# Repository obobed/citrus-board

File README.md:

# Citrus Board
A RP2350 based devboard with LiPO and HSTX support!

## Why I made this + features
I made this since I wanted an alternative to the mainstream RP2350/2040 boards (like the xiaos), but with support for the more niche features of the chip that aren't exposed on almost all of them, like HSTX ([page 1203](https://pip-assets.raspberrypi.com/categories/1214-rp2350/documents/RP-008373-DS-2-rp2350-datasheet.pdf#page=1203)), which allows you to easily add an external display (or even camera) without sacrificing a lot the small computing power of the small chip, or even LiPo support (although most boards have it (except for the Raspberry Pi Pico), many don't have a dedicated charging IC to both support the chip's usage and to charge the battery at the same time). Additionally, it has 26 pins, indicator LEDs for charging and power, the HSTX 22pin ribbon cable terminal (which can be used with libraries like [this](https://github.com/adafruit/Adafruit-DVI-HSTX) from Adafruit) and a debug connector that is exactly compatible with the oficial [Raspberry Pi Debug Probe
](https://www.raspberrypi.com/documentation/microcontrollers/debug-probe.html).

## Repo Structure
* [/pcb](/pcb) - My KiCad design files
* [/production](/production) - Everything you need to manufacture your own! Includes gerbers, a bom and positioning files
* [/images](/images) - Images of my PCB and 3D view! (Zine is in [/zine](/zine))
* [/plots](/plots) - Schematic plot (SVG and PNG) and separate layer outlines in DXF format
* [/cad](/cad) - A step file of my PCB for reference when building projects around it
* [/bom](/bom) - My BOMs (like the below tables) stored in a CSV format

## Schematic

## PCB

## 3D View

## Assembly
Welll this is a devboard, so there isn't much to assemble, but if you want to hand solder (definitely do not reccomend) instead of doing PCBA, follow these steps (my bom at the bottom accounts for using PCBA and not hand soldering)
Prerequisite:
* Purchase a stencil from JLCPCB alongside your order, and use the [LCSC BOM](/bom/component_bom.csv) to buy the separate parts from LCSC

1. Apply the paste
2. Place components
3. Use your preferred equipment (oven, hot-air gun or hotplate) to solder the board
4. Done!

(this section is here because the submission precheck kept giving me warning about this)

## BOM
### Component BOM
| Designator                                           | Footprint                                            | Quantity | Value                                | LCSC Part # | Total Cost (USD) |
|------------------------------------------------------|------------------------------------------------------|----------|--------------------------------------|-------------|------------------|
| C1, C2                                               | 0402                                                 | 2        | 15p                                  | C1548       | 0.0088           |
| C10, C12, C14, C5, C6, C9                            | 0402                                                 | 6        | 4.7u                                 | C23733      | 0.2328           |
| C11, C13, C17, C18, C19, C20, C21, C22, C23, C27, C8 | 0402                                                 | 11       | 100n                                 | C307331     | 0.0682           |
| C15, C16, C4, C7                                     | 0805                                                 | 4        | 10u                                  | C1713       | 1.6848           |
| C3                                                   | 603                                                  | 1        | 1u                                   | C1592       | 0.0312           |
| D1                                                   | 0805                                                 | 1        | ORANGE                               | C2296       | 0.0304           |
| D2                                                   | 0603                                                 | 1        | RED                                  | C2286       | 0.0144           |
| J1                                                   | USB-C-SMD_TYPE-C-6PIN-2MD-073                        | 1        | SHOU_HAN_USB_C_Receptacle_USB2.0_16P |             | 0.2205           |
| J2                                                   | JST_PH_B2B-PH-K_1x02_P2.00mm_Vertical                | 1        | Conn_01x02                           | C131337     | 0.1041           |
| J3                                                   | JST_SH_SM03B-SRSS-TB_1x03-1MP_P1.00mm_Horizontal     | 1        | Conn_01x03_MountingPin               | C160389     | 1.3305           |
| J4                                                   | CONN-SMD_AFC01-S22FCA-HF                             | 1        | 0.5mm FPC                            | C49260526   | 0.2614           |
| L1                                                   | IND-SMD_L3.9-W3.9                                    | 1        | 2.2uH                                | C20416998   | 2.2494           |
| L2                                                   | IND-SMD_L2.0-W1.6_AOTA-B201610S3R3-101-T             | 1        | 3.3uH                                | C42411119   | 1.4085           |
| R1                                                   | 0402                                                 | 1        | 1.18k                                | C270651     | 0.01             |
| R10                                                  | 0402                                                 | 1        | 1k                                   | C270651     | 0.0022           |
| R11                                                  | 0402                                                 | 1        | 33R                                  | C25105      | 0.002            |
| R12, R15, R17, R6                                    | 0402                                                 | 4        | 10k                                  | C25744      | 0.0232           |
| R13, R14                                             | 0402                                                 | 2        | 27R                                  | C25100      | 0.02             |
| R16                                                  | 0805                                                 | 1        | 0                                    | C17477      | 0.006            |
| R2                                                   | 0402                                                 | 1        | 1.13k                                | C67014      | 0.018            |
| R3                                                   | 0402                                                 | 1        | 50                                   | C227387     | 0.016            |
| R4, R5                                               | 0402                                                 | 2        | 5k1                                  | C25905      | 0.0036           |
| R7                                                   | 0402                                                 | 1        | 1.5k                                 | C25867      | 0.0022           |
| R8                                                   | 0402                                                 | 1        | 100                                  | C25076      | 0.0024           |
| R9                                                   | 0402                                                 | 1        | 100k                                 | C25741      | 0.0078           |
| SW1, SW2                                             | SW-SMD_L3.9-W3.0-P4.45                               | 2        | SW_Push                              | C720477     | 0.2208           |
| U1                                                   | VQFN-16-1EP_3x3mm_P0.5mm_EP1.6x1.6mm                 | 1        | BQ24074RGT                           | C54313      | 4.7728           |
| U2                                                   | Texas_DRC0010J_ThermalVias                           | 1        | TPS63000-Q1                          | C28060      | 3.5514           |
| U3                                                   | RP2350-QFN-60-1EP_7x7_P0.4mm_EP3.4x3.4mm_ThermalVias | 1        | RP2354A                              | C41378174   | 2.678            |
| U4                                                   | SOIC-8_5.3x5.3mm_P1.27mm                             | 1        | W25Q128JVS                           | C97521      | 4.8534           |
| Y1                                                   | Crystal_SMD_3225-4Pin_3.2x2.5mm                      | 1        | Crystal_GND24                        | C20625731   | 1.4655           |
|||||||
| Total                                                |                                                      |          |                                      |             | 25.3003          |

### Overall BOM
| Item              | Cost (USD) | Notes |
|-------------------|------------|-------|
| PCB               | $7         |       |
| Castellated Edges | $37.70     | Not strictly required, see note 2 [here](https://jlcpcb.com/help/article/what-is-castellated-holes). If you want to save on costs, it is not necessary, but will result in a slightly lower quality finish. |
| PCB Shipping      | $1.50      |       |
| PCBA              | $80.72     |       |
||||
| Total | $89.22 ||

## Zine!!

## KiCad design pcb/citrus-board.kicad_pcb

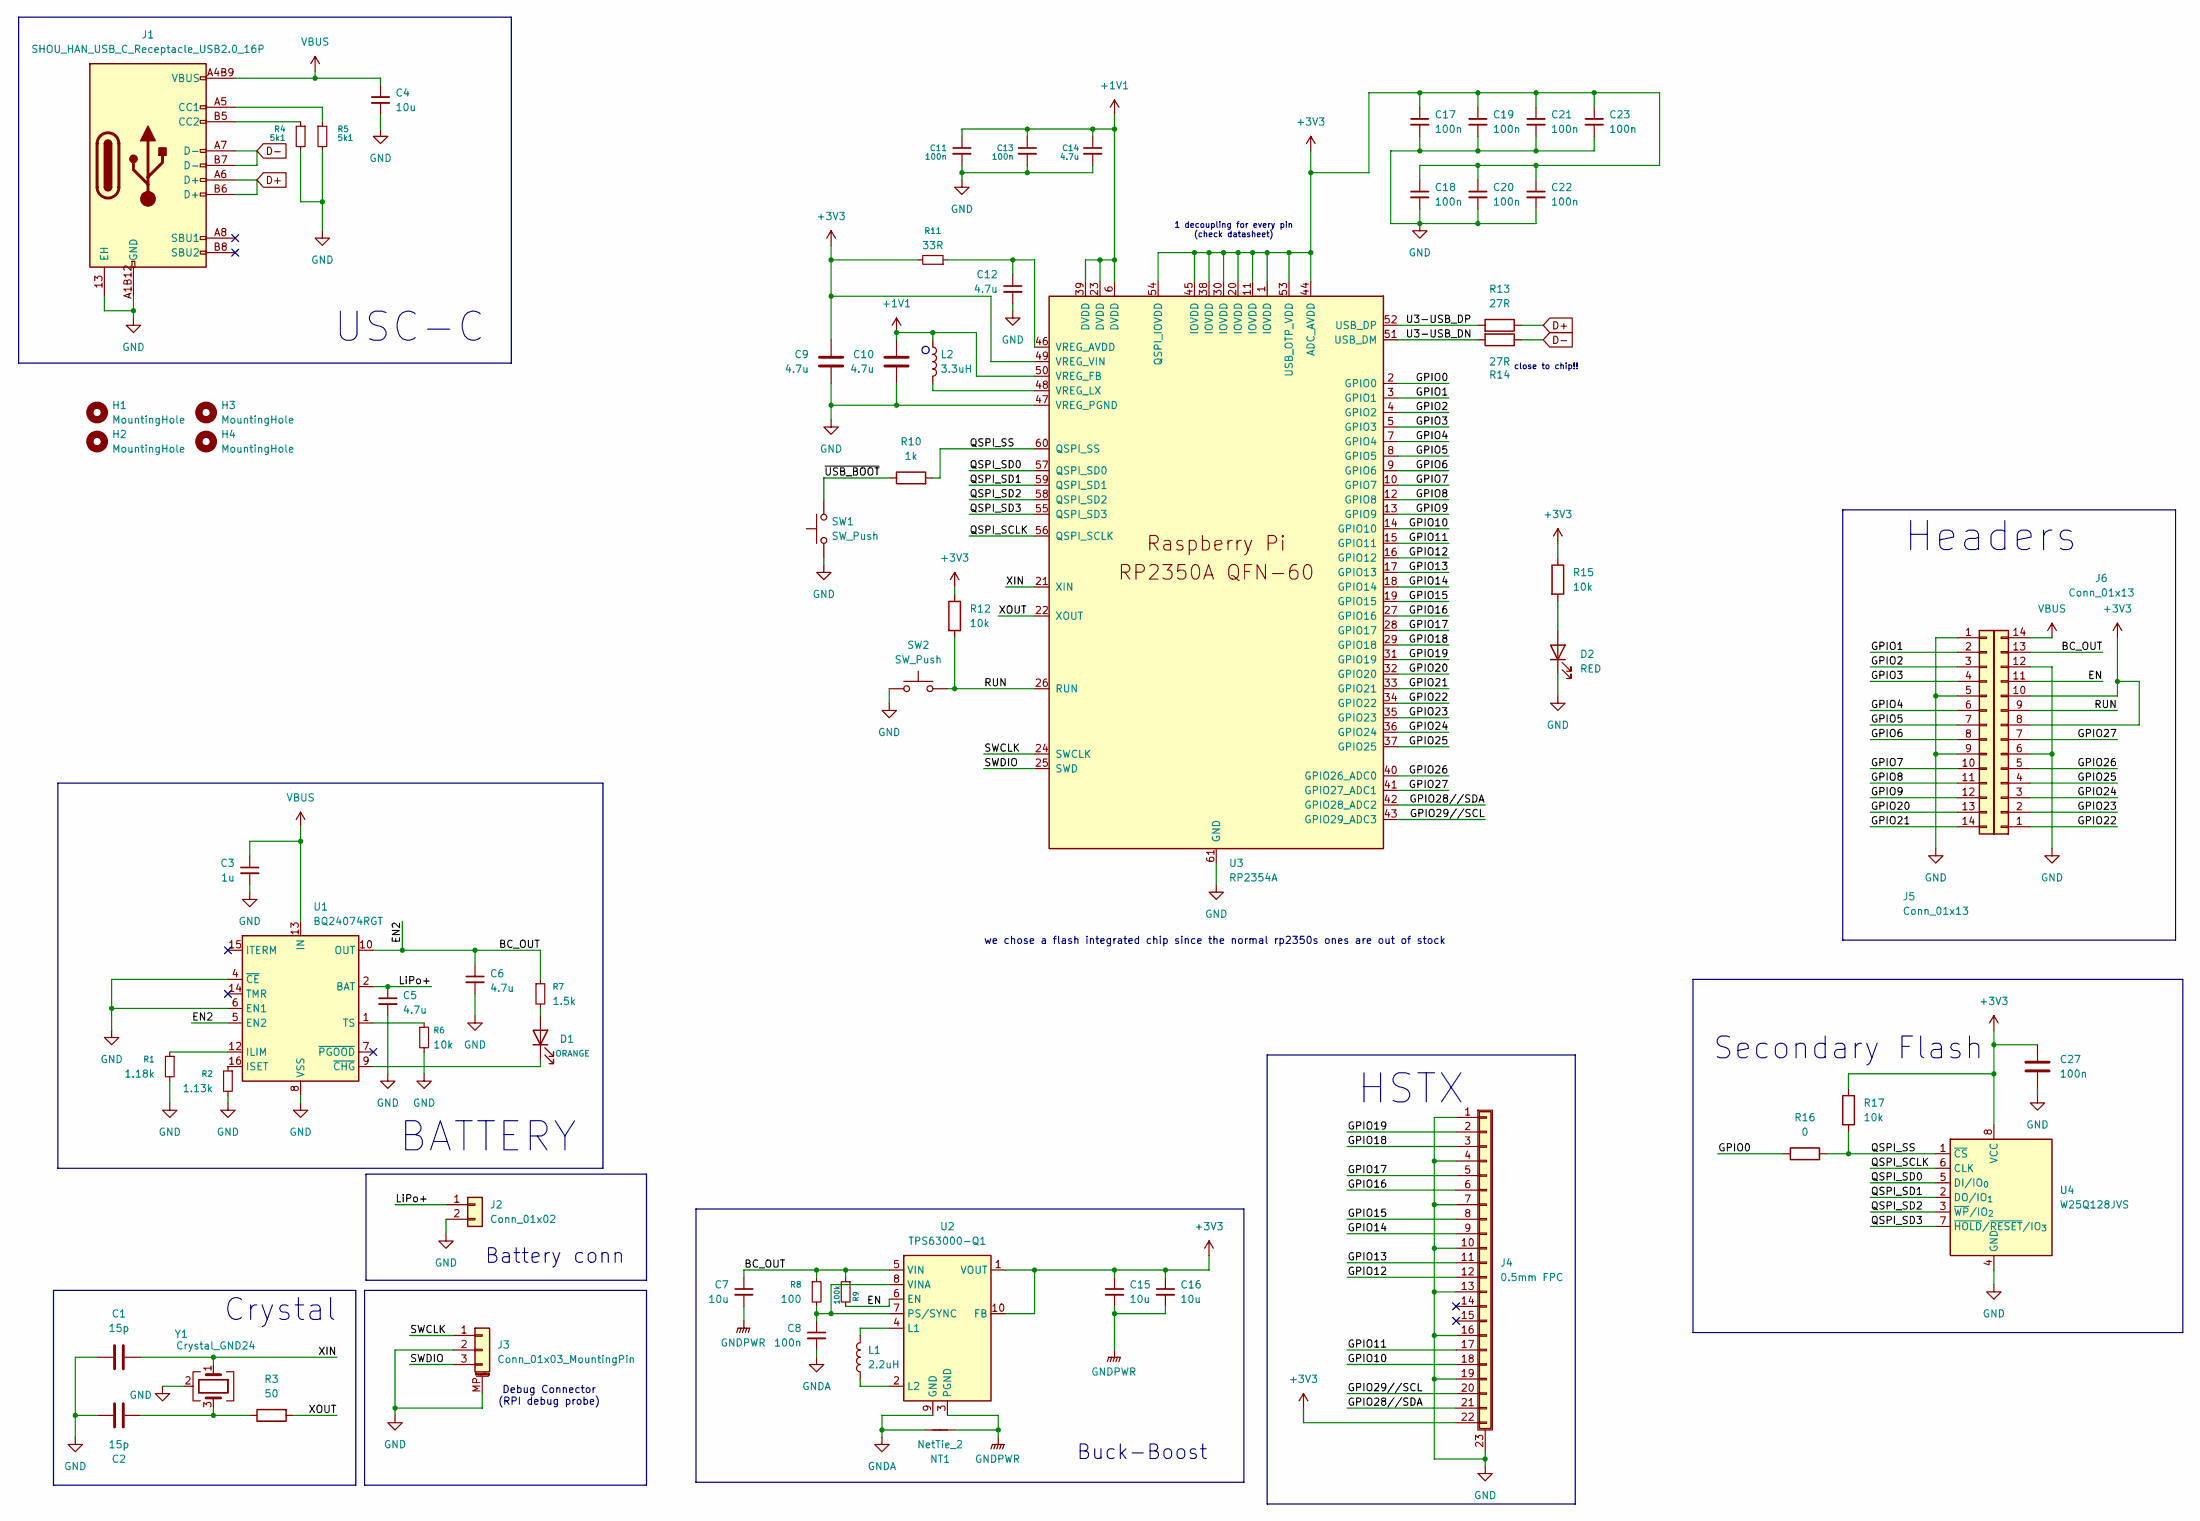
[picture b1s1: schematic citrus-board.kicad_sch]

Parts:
C1, C2: 15p; C_0402_1005Metric; LCSC Part # C1548
C3: 1u; C_0603_1608Metric; LCSC Part # C1592
C4, C7, C15, C16: 10u; C_0805_2012Metric; LCSC Part # C1713
C5, C6, C9, C10, C12, C14: 4.7u; C_0402_1005Metric; LCSC Part # C23733
C8, C11, C13, C17, C18, C19, C20, C21, C22, C23, C27: 100n; C_0402_1005Metric; LCSC Part # C307331
D1: ORANGE; LED_0805_2012Metric; LCSC Part # C2296
D2: RED; LED_0603_1608Metric; LCSC Part # C2286
H1, H2, H3, H4: MountingHole; MountingHole_2.1mm
J1: SHOU_HAN_USB_C_Receptacle_USB2.0_16P; USB-C-SMD_TYPE-C-6PIN-2MD-073; LCSC Part # C2765186
J2: Conn_01x02; JST_PH_B2B-PH-K_1x02_P2.00mm_Vertical; LCSC Part # C131337
J3: Conn_01x03_MountingPin; JST_SH_SM03B-SRSS-TB_1x03-1MP_P1.00mm_Horizontal; LCSC Part # C160389
J4: 0.5mm FPC; CONN-SMD_AFC01-S22FCA-HF; LCSC Part # C49260526
J5, J6: Conn_01x13; Conn_01x14_Castellated
L1: 2.2uH; IND-SMD_L3.9-W3.9; LCSC Part # C20416998
L2: 3.3uH; IND-SMD_L2.0-W1.6_AOTA-B201610S3R3-101-T; LCSC Part # C42411119
NT1: NetTie_2; NetTie-2_SMD_Pad0.5mm
R1: 1.18k; R_0402_1005Metric; LCSC Part # C270651
R2: 1.13k; R_0402_1005Metric; LCSC Part # C67014
R3: 50; R_0402_1005Metric; LCSC Part # C227387
R4, R5: 5k1; R_0402_1005Metric; LCSC Part # C25905
R6, R12, R15, R17: 10k; R_0402_1005Metric; LCSC Part # C25744
R7: 1.5k; R_0402_1005Metric; LCSC Part # C25867
R8: 100; R_0402_1005Metric; LCSC Part # C25076
R9: 100k; R_0402_1005Metric; LCSC Part # C25741
R10: 1k; R_0402_1005Metric; LCSC Part # C270651
R11: 33R; R_0402_1005Metric; LCSC Part # C25105
R13, R14: 27R; R_0402_1005Metric; LCSC Part # C25100
R16: 0; R_0805_2012Metric; LCSC Part # C17477
SW1, SW2: SW_Push; SW-SMD_L3.9-W3.0-P4.45; LCSC Part # C720477
U1: BQ24074RGT; VQFN-16-1EP_3x3mm_P0.5mm_EP1.6x1.6mm; LCSC Part # C54313
U2: TPS63000-Q1; Texas_DRC0010J_ThermalVias; LCSC Part # C28060
U3: RP2354A; RP2350-QFN-60-1EP_7x7_P0.4mm_EP3.4x3.4mm_ThermalVias; LCSC Part # C41378174
U4: W25Q128JVS; SOIC-8_5.3x5.3mm_P1.27mm; LCSC Part # C97521
Y1: Crystal_GND24; Crystal_SMD_3225-4Pin_3.2x2.5mm; LCSC Part # C20625731

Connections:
+1V1: C10.1, C11.1, C13.1, C14.1, L2.1, U3.6 (DVDD), U3.23 (DVDD), U3.39 (DVDD), U3.50 (VREG_FB)
+3V3: C9.1, C15.1, C16.1, C17.1, C18.1, C19.1, C20.1, C21.1, C22.1, C23.1, C27.1, J4.22, J6.8, J6.10, R11.2, R12.1, R15.1, R17.2, U2.1 (VOUT), U2.10 (FB), U3.1 (IOVDD), U3.11 (IOVDD), U3.20 (IOVDD), U3.30 (IOVDD), U3.38 (IOVDD), U3.44 (ADC_AVDD), U3.45 (IOVDD), U3.49 (VREG_VIN), U3.53 (USB_OTP_VDD), U3.54 (QSPI_IOVDD), U4.8 (VCC)
/BC_OUT: C6.1, C7.1, J6.13, R7.1, R8.1, R9.1, U1.5 (EN2), U1.10 (OUT), U1.11 (OUT), U2.5 (VIN)
/EN: J6.11, R9.2, U2.6 (EN)
/GPIO0: R16.1, U3.2 (GPIO0)
/GPIO1: J5.2, U3.3 (GPIO1)
/GPIO2: J5.3, U3.4 (GPIO2)
/GPIO3: J5.4, U3.5 (GPIO3)
/GPIO4: J5.6, U3.7 (GPIO4)
/GPIO5: J5.7, U3.8 (GPIO5)
/GPIO6: J5.8, U3.9 (GPIO6)
/GPIO7: J5.10, U3.10 (GPIO7)
/GPIO8: J5.11, U3.12 (GPIO8)
/GPIO9: J5.12, U3.13 (GPIO9)
/GPIO10: J4.18, U3.14 (GPIO10)
/GPIO11: J4.17, U3.15 (GPIO11)
/GPIO12: J4.12, U3.16 (GPIO12)
/GPIO13: J4.11, U3.17 (GPIO13)
/GPIO14: J4.9, U3.18 (GPIO14)
/GPIO15: J4.8, U3.19 (GPIO15)
/GPIO16: J4.6, U3.27 (GPIO16)
/GPIO17: J4.5, U3.28 (GPIO17)
/GPIO18: J4.3, U3.29 (GPIO18)
/GPIO19: J4.2, U3.31 (GPIO19)
/GPIO20: J5.13, U3.32 (GPIO20)
/GPIO21: J5.14, U3.33 (GPIO21)
/GPIO22: J6.1, U3.34 (GPIO22)
/GPIO23: J6.2, U3.35 (GPIO23)
/GPIO24: J6.3, U3.36 (GPIO24)
/GPIO25: J6.4, U3.37 (GPIO25)
/GPIO26: J6.5, U3.40 (GPIO26_ADC0)
/GPIO27: J6.7, U3.41 (GPIO27_ADC1)
/GPIO28//SDA: J4.21, U3.42 (GPIO28_ADC2)
/GPIO29//SCL: J4.20, U3.43 (GPIO29_ADC3)
/LiPo+: C5.1, J2.1, U1.2 (BAT), U1.3 (BAT)
/QSPI_SCLK: U3.56 (QSPI_SCLK), U4.6 (CLK)
/QSPI_SD0: U3.57 (QSPI_SD0), U4.5 (DI/IO_{0})
/QSPI_SD1: U3.59 (QSPI_SD1), U4.2 (DO/IO_{1})
/QSPI_SD2: U3.58 (QSPI_SD2), U4.3 (~WP/IO_{2})
/QSPI_SD3: U3.55 (QSPI_SD3), U4.7 (~HOLD/~RESET/IO_{3})
/QSPI_SS: R10.2, R16.2, R17.1, U3.60 (QSPI_SS), U4.1 (~CS)
/RUN: J6.9, R12.2, SW2.2, U3.26 (RUN)
/SWCLK: J3.1, U3.24 (SWCLK)
/SWDIO: J3.3, U3.25 (SWD)
/U3-USB_DN: R14.2, U3.51 (USB_DM)
/U3-USB_DP: R13.2, U3.52 (USB_DP)
/XIN: C1.2, U3.21 (XIN), Y1.1
/XOUT: R3.2, U3.22 (XOUT)
/~USB_BOOT: R10.1, SW1.2
D+: J1.A6 (D+), J1.B6 (D+), R13.1
D-: J1.A7 (D-), J1.B7 (D-), R14.1
GND: C1.1, C2.1, C3.2, C4.2, C5.2, C6.2, C9.2, C10.2, C11.2, C12.2, C13.2, C14.2, C17.2, C18.2, C19.2, C20.2, C21.2, C22.2, C23.2, C27.2, D2.1 (K), J1.13 (EH), J1.14 (EH), J1.A1B12 (GND), J1.B1A12 (GND), J2.2, J3.2, J3.MP (MountPin), J4.1, J4.4, J4.7, J4.10, J4.13, J4.16, J4.19, J4.23 (Shield), J4.24 (Shield), J5.1, J5.5, J5.9, J6.6, J6.12, R1.2, R2.2, R4.2, R5.2, R6.2, SW1.1, SW2.1, U1.4 (~CE), U1.6 (EN1), U1.8 (VSS), U1.17 (VSS), U3.47 (VREG_PGND), U3.61 (GND), U4.4 (GND), Y1.2 (G), Y1.4 (G)
GNDA: C8.2, NT1.1, U2.9 (GND)
GNDPWR: C7.2, C15.2, C16.2, NT1.2, U2.3 (PGND), U2.11 (PGND)
unnamed: C2.2, R3.1, Y1.3
unnamed: D1.2 (A), R7.2
unnamed: D1.1 (K), U1.9 (~CHG)
unnamed: D2.2 (A), R15.2
unnamed: J1.A5 (CC1), R5.1
unnamed: J1.B5 (CC2), R4.1
unnamed: R1.1, U1.12 (ILIM)
unnamed: R2.1, U1.16 (ISET)
unnamed: R6.1, U1.1 (TS)
unnamed: L1.2, U2.4 (L1)
unnamed: L1.1, U2.2 (L2)
unnamed: C8.1, R8.2, U2.7 (PS/SYNC), U2.8 (VINA)
unnamed: C12.1, R11.1, U3.46 (VREG_AVDD)
unnamed: L2.2, U3.48 (VREG_LX)
VBUS: C3.1, C4.1, J1.A4B9 (VBUS), J1.B4A9 (VBUS), J6.14, U1.13 (IN)

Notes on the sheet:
HSTX
USC-C
Headers
Crystal
1 decoupling for every pin (check datasheet)
close to chip!!
Debug Connector (RPI debug probe)
Buck-Boost
Battery conn
we chose a flash integrated chip since the normal rp2350s ones are out of stock
Secondary Flash
BATTERY

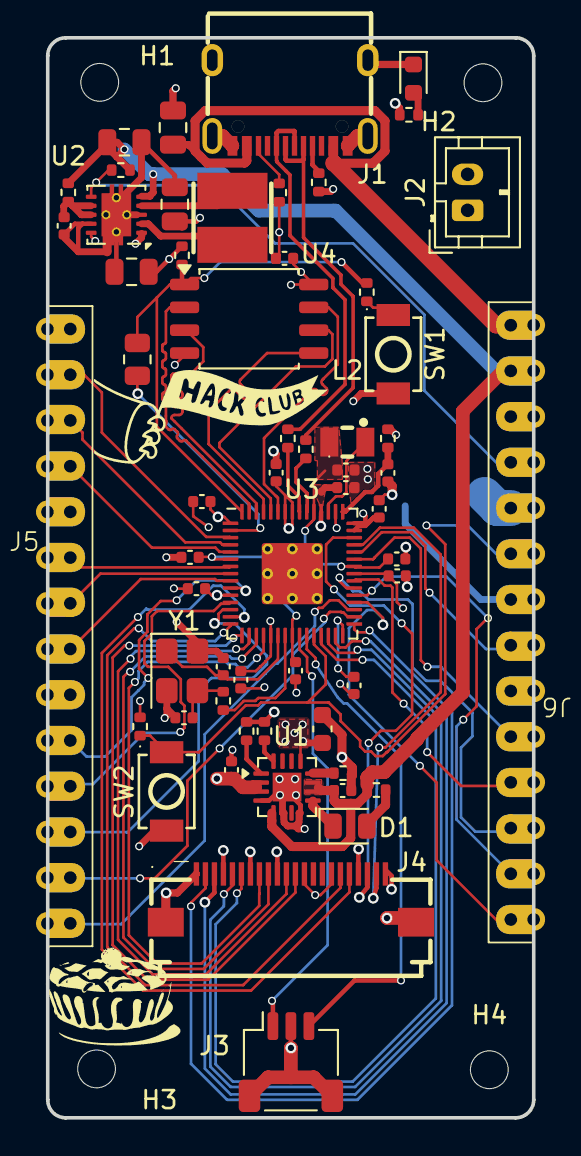
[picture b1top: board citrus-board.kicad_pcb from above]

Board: 4 copper layers, 27.0 x 60.0 mm, 63 parts (0 on the bottom side), 69 nets.

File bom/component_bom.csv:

Designator,Footprint,Quantity,Value,LCSC Part #,Total Cost (USD)
"C1, C2",0402,2,15p,C1548,0.0088
"C10, C12, C14, C5, C6, C9",0402,6,4.7u,C23733,0.2328
"C11, C13, C17, C18, C19, C20, C21, C22, C23, C27, C8",0402,11,100n,C307331,0.0682
"C15, C16, C4, C7",0805,4,10u,C1713,1.6848
C3,603,1,1u,C1592,0.0312
D1,0805,1,ORANGE,C2296,0.0304
D2,0603,1,RED,C2286,0.0144
J1,USB-C-SMD_TYPE-C-6PIN-2MD-073,1,SHOU_HAN_USB_C_Receptacle_USB2.0_16P,,0.2205
J2,JST_PH_B2B-PH-K_1x02_P2.00mm_Vertical,1,Conn_01x02,C131337,0.1041
J3,JST_SH_SM03B-SRSS-TB_1x03-1MP_P1.00mm_Horizontal,1,Conn_01x03_MountingPin,C160389,1.3305
J4,CONN-SMD_AFC01-S22FCA-HF,1,0.5mm FPC,C49260526,0.2614
L1,IND-SMD_L3.9-W3.9,1,2.2uH,C20416998,2.2494
L2,IND-SMD_L2.0-W1.6_AOTA-B201610S3R3-101-T,1,3.3uH,C42411119,1.4085
R1,0402,1,1.18k,C270651,0.01
R10,0402,1,1k,C270651,0.0022
R11,0402,1,33R,C25105,0.002
"R12, R15, R17, R6",0402,4,10k,C25744,0.0232
"R13, R14",0402,2,27R,C25100,0.02
R16,0805,1,0,C17477,0.006
R2,0402,1,1.13k,C67014,0.018
R3,0402,1,50,C227387,0.016
"R4, R5",0402,2,5k1,C25905,0.0036
R7,0402,1,1.5k,C25867,0.0022
R8,0402,1,100,C25076,0.0024
R9,0402,1,100k,C25741,0.0078
"SW1, SW2",SW-SMD_L3.9-W3.0-P4.45,2,SW_Push,C720477,0.2208
U1,VQFN-16-1EP_3x3mm_P0.5mm_EP1.6x1.6mm,1,BQ24074RGT,C54313,4.7728
U2,Texas_DRC0010J_ThermalVias,1,TPS63000-Q1,C28060,3.5514
U3,RP2350-QFN-60-1EP_7x7_P0.4mm_EP3.4x3.4mm_ThermalVias,1,RP2354A,C41378174,2.678
U4,SOIC-8_5.3x5.3mm_P1.27mm,1,W25Q128JVS,C97521,4.8534
Y1,Crystal_SMD_3225-4Pin_3.2x2.5mm,1,Crystal_GND24,C20625731,1.4655
Total,,,,,25.3003

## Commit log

2026-06-17 finish schema!
    todo:
    pcb
    clean up folders
2026-06-20 finish routing
2026-06-20 zine + rotate debug connector
2026-06-20 update fields + production export
2026-06-20 fillets? never heard of er
2026-06-20 oop forgot to save :sob:
2026-06-20 images + restructure
2026-06-20 README
2026-06-20 no boms?? also buns ahh gitignore
2026-06-21 castellated holes + better silkscreen + new images
2026-06-21 "complex signals like usb" holy sleep deprivation anyways we updated the zine images
2026-06-21 fix drc and better readme
2026-06-21 README (assembly)
2026-06-21 hopefully the fallout precheck picks up on this?
2026-06-21 woah crazy it did actually
